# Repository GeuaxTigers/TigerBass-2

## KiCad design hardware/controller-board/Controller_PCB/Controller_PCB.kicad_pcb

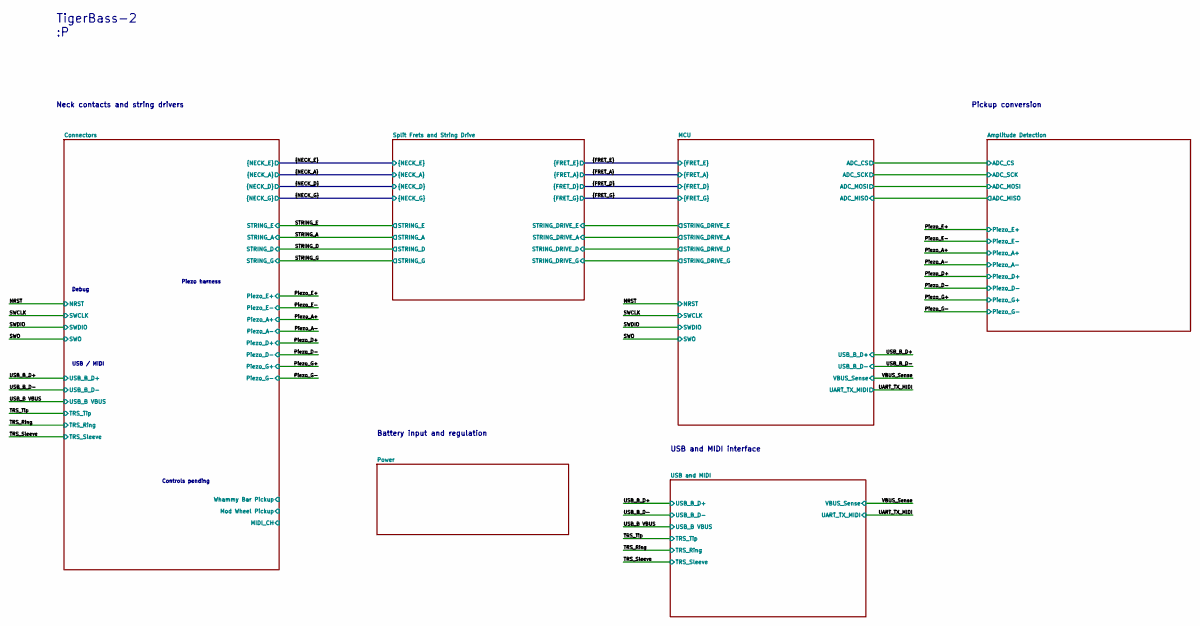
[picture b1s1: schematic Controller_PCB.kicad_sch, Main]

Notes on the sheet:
Pickup conversion
USB and MIDI interface
Debug
Controls pending
Battery input and regulation
Neck contacts and string drivers
Piezo harness
TigerBass-2 :P
USB / MIDI

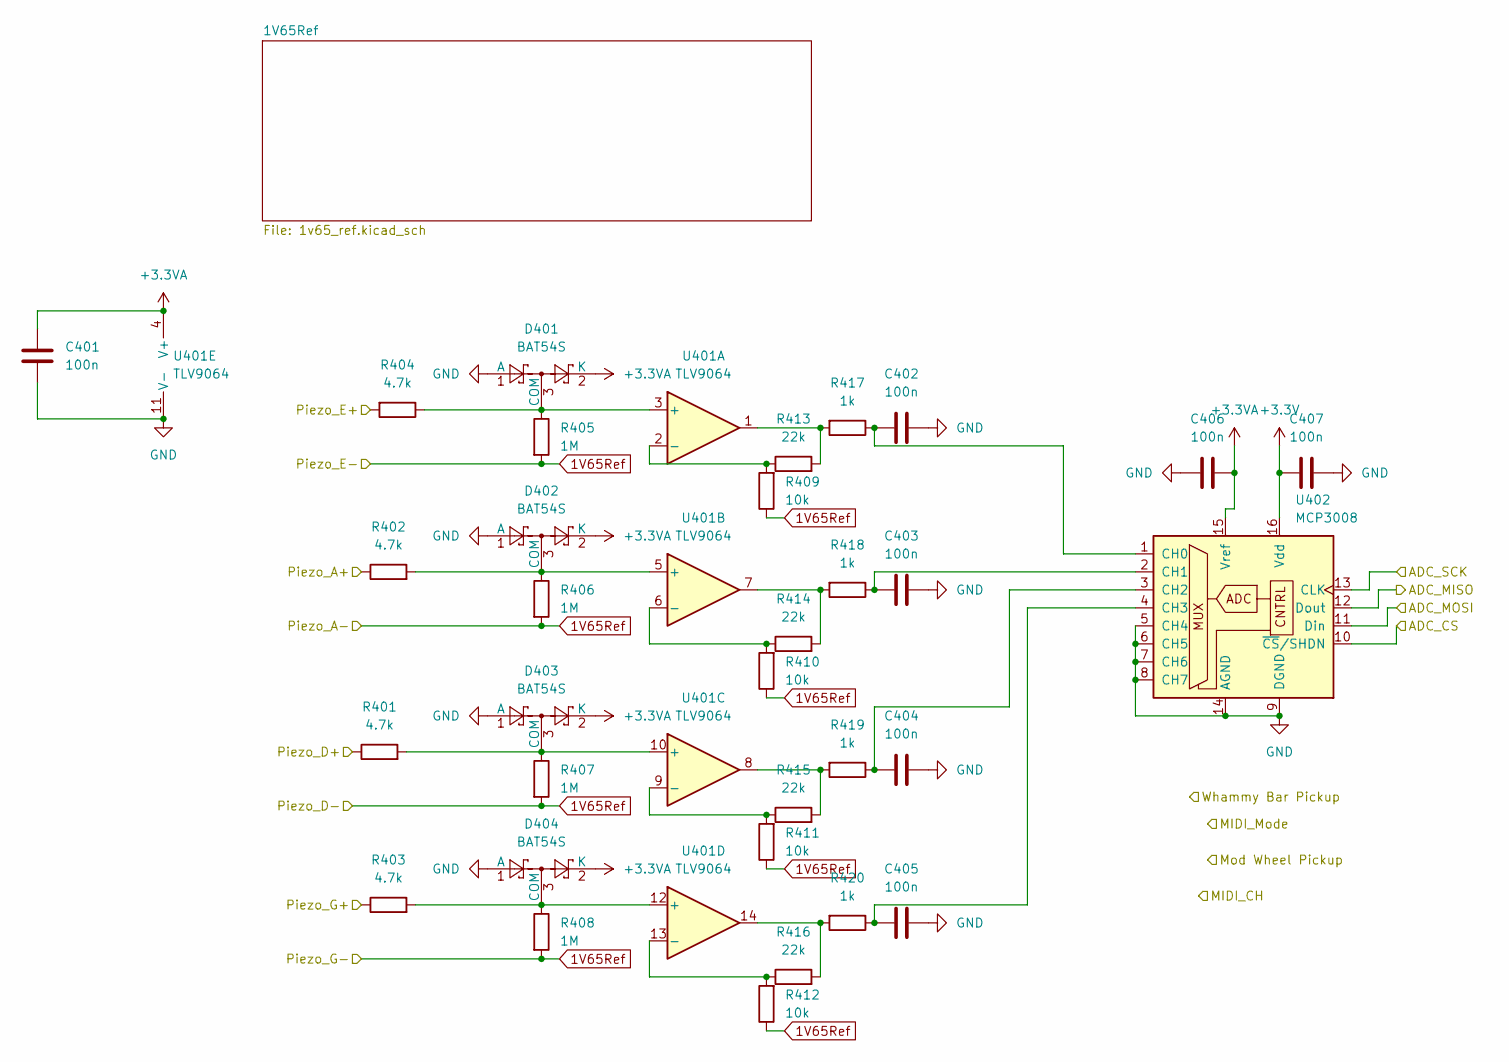
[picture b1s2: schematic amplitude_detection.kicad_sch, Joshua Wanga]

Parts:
C401, C402, C403, C404, C405, C406, C407: 100n; C_0402_1005Metric
D401, D402, D403, D404: BAT54S; SOT-23
R401, R402, R403, R404: 4.7k; R_0402_1005Metric
R405, R406, R407, R408: 1M; R_0402_1005Metric
R409, R410, R411, R412: 10k; R_0402_1005Metric
R413, R414, R415, R416: 22k; R_0402_1005Metric
R417, R418, R419, R420: 1k; R_0402_1005Metric
U401: TLV9064; SOIC127P600X175-14N
U402: MCP3008; SOIC127P600X175-16N

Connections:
1V65Ref: R405.2, R406.2, R407.2, R408.2, R409.1, R410.1, R411.1, R412.1; also elsewhere on the board
+3.3V: C407.1, U402.16 (Vdd); also elsewhere on the board
+3.3VA: C401.2, C406.1, D401.2 (K), D402.2 (K), D403.2 (K), D404.2 (K), U401.4 (V+), U402.15 (Vref); also elsewhere on the board
/Piezo_A+: R402.1
/Piezo_D+: R401.1
/Piezo_E+: R404.2
/Piezo_G+: R403.1
GND: C401.1, C402.2, C403.2, C404.2, C405.2, C406.2, C407.2, D401.1 (A), D402.1 (A), D403.1 (A), D404.1 (A), U401.11 (V-), U402.5 (CH4), U402.6 (CH5), U402.7 (CH6), U402.8 (CH7), U402.9 (DGND), U402.14 (AGND); also elsewhere on the board
unnamed: D401.3 (COM), R404.1, R405.1, U401.3 (+)
unnamed: D402.3 (COM), R402.2, R406.1, U401.5 (+)
unnamed: D403.3 (COM), R401.2, R407.1, U401.10 (+)
unnamed: D404.3 (COM), R403.2, R408.1, U401.12 (+)
unnamed: R413.2, R417.2, U401.1
unnamed: R414.2, R418.2, U401.7
unnamed: R415.2, R419.2, U401.8
unnamed: R416.2, R420.2, U401.14
unnamed: R409.2, R413.1, U401.2 (-)
unnamed: R410.2, R414.1, U401.6 (-)
unnamed: R411.2, R415.1, U401.9 (-)
unnamed: R412.2, R416.1, U401.13 (-)
unnamed: C402.1, R417.1, U402.1 (CH0)
unnamed: C403.1, R418.1, U402.2 (CH1)
unnamed: C404.1, R419.1, U402.3 (CH2)
unnamed: C405.1, R420.1, U402.4 (CH3)

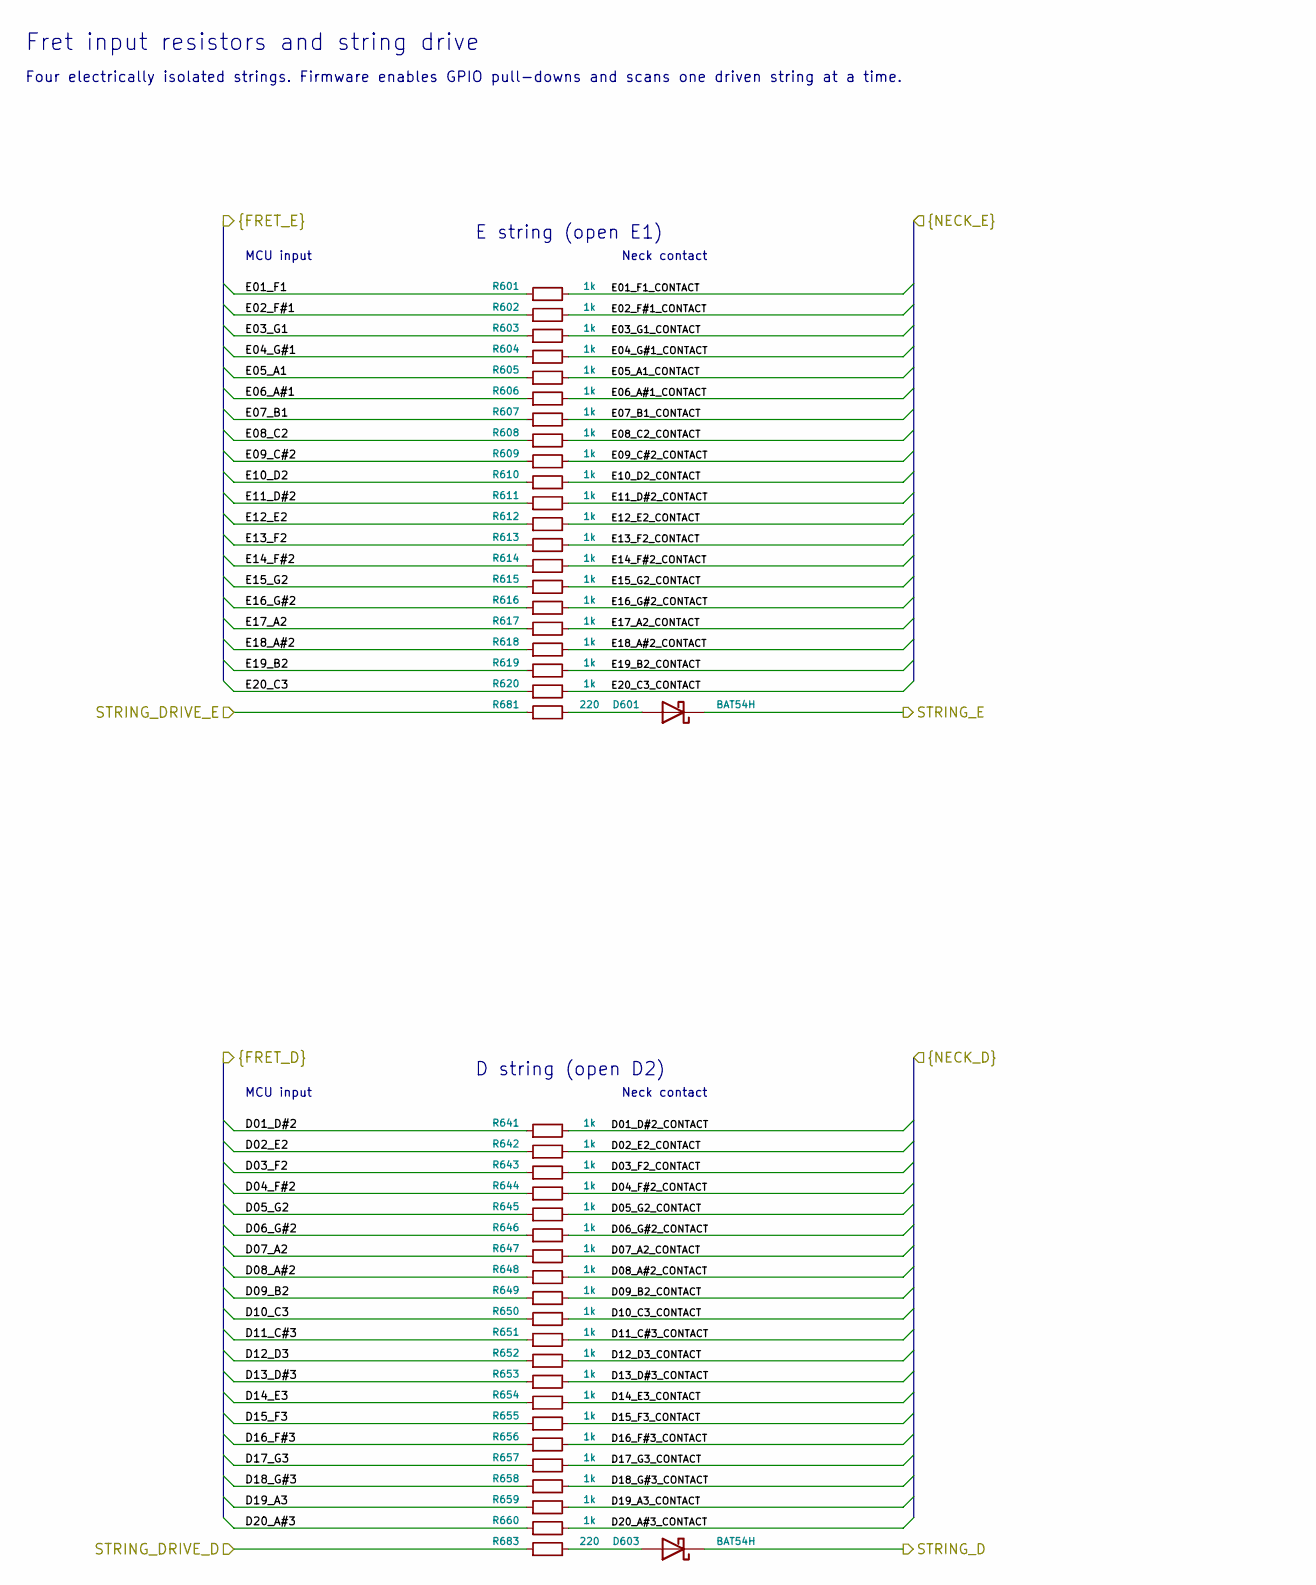
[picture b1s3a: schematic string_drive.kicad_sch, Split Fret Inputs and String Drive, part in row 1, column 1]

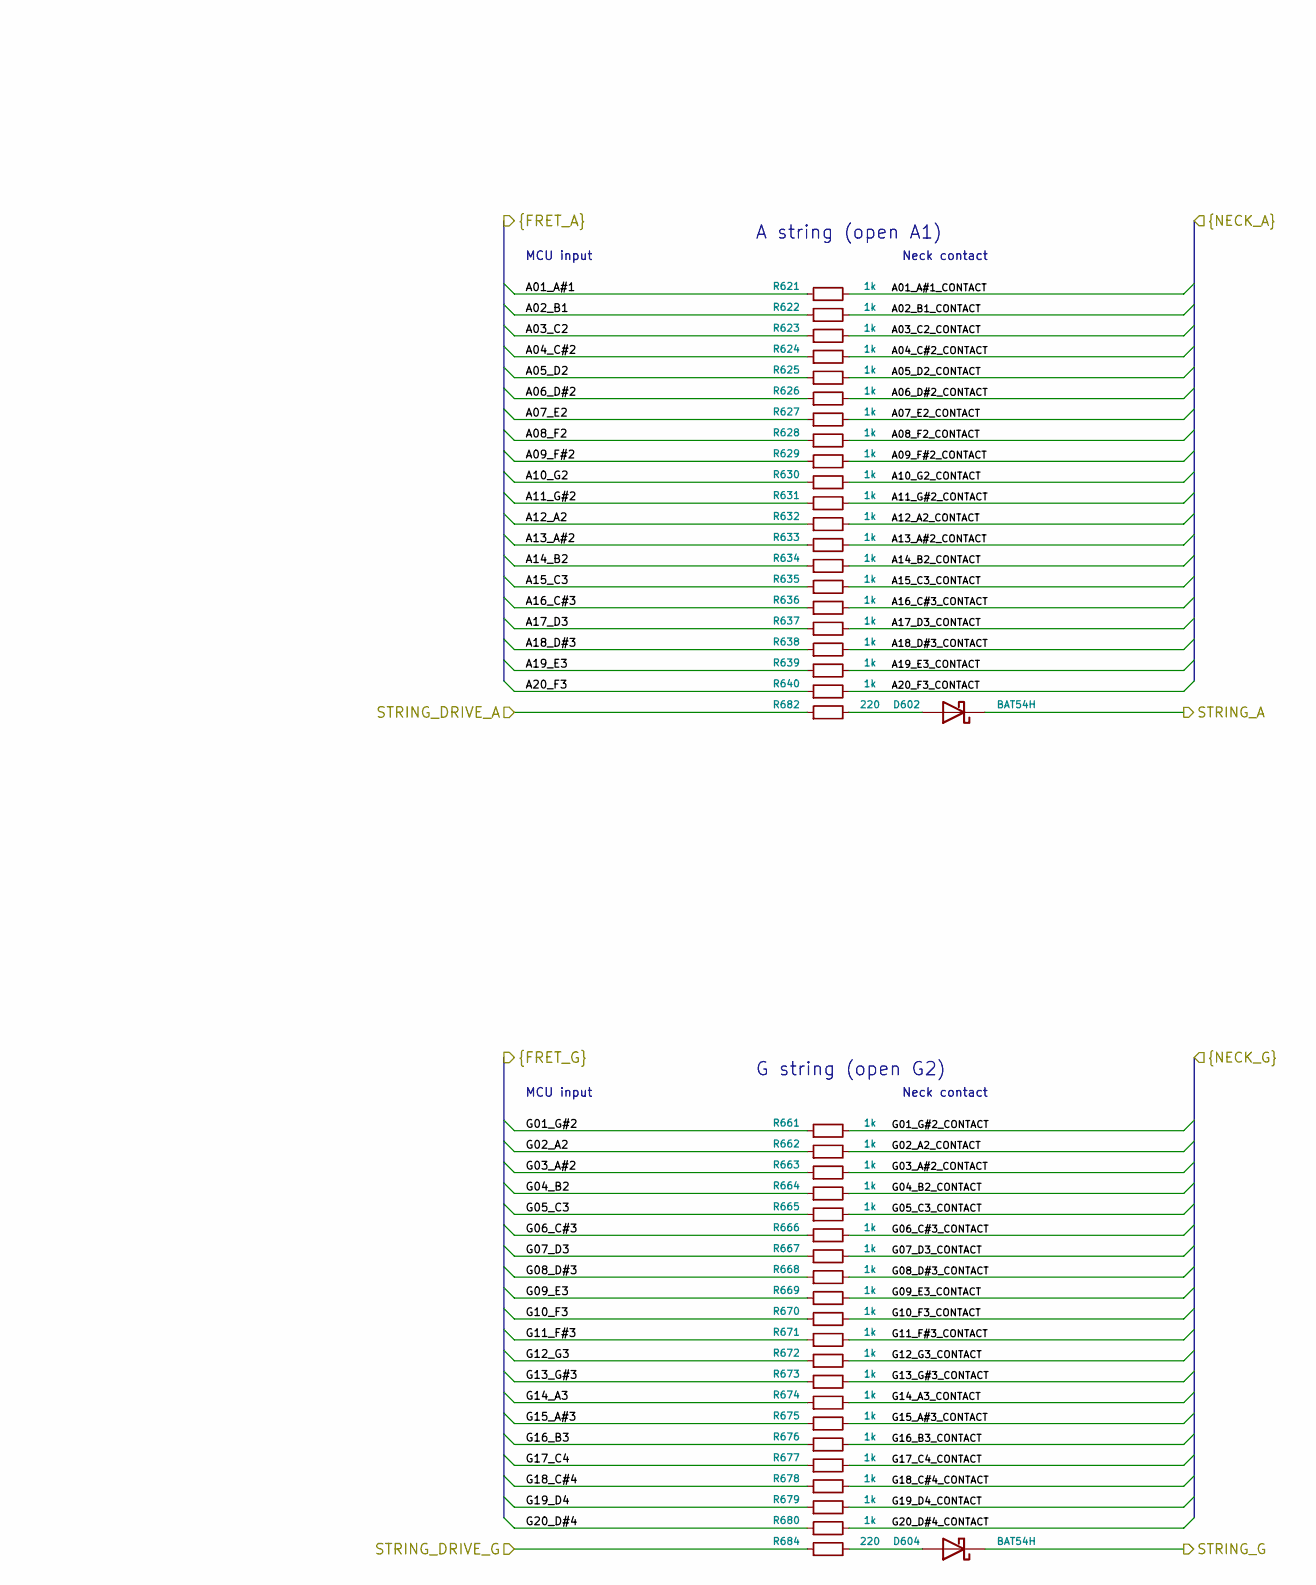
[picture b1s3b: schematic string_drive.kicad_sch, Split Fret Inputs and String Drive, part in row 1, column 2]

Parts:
D601, D602, D603, D604: BAT54H; D_SOD-123F
R601, R602, R603, R604, R605, R606, R607, R608, R609, R610, R611, R612, R613, R614, R615, R616, R617, R618, R619, R620, R621, R622, R623, R624, R625, R626, R627, R628, R629, R630, R631, R632, R633, R634, R635, R636, R637, R638, R639, R640, R641, R642, R643, R644, R645, R646, R647, R648, R649, R650, R651, R652, R653, R654, R655, R656, R657, R658, R659, R660, R661, R662, R663, R664, R665, R666, R667, R668, R669, R670, R671, R672, R673, R674, R675, R676, R677, R678, R679, R680: 1k; R_0603_1608Metric
R681, R682, R683, R684: 220; R_0603_1608Metric

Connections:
/A01_A#1: R621.1; also elsewhere on the board
/A01_A#1_CONTACT: R621.2; also elsewhere on the board
/A02_B1: R622.1; also elsewhere on the board
/A02_B1_CONTACT: R622.2; also elsewhere on the board
/A03_C2: R623.1; also elsewhere on the board
/A03_C2_CONTACT: R623.2; also elsewhere on the board
/A04_C#2: R624.1; also elsewhere on the board
/A04_C#2_CONTACT: R624.2; also elsewhere on the board
/A05_D2: R625.1; also elsewhere on the board
/A05_D2_CONTACT: R625.2; also elsewhere on the board
/A06_D#2: R626.1; also elsewhere on the board
/A06_D#2_CONTACT: R626.2; also elsewhere on the board
/A07_E2: R627.1; also elsewhere on the board
/A07_E2_CONTACT: R627.2; also elsewhere on the board
/A08_F2: R628.1; also elsewhere on the board
/A08_F2_CONTACT: R628.2; also elsewhere on the board
/A09_F#2: R629.1; also elsewhere on the board
/A09_F#2_CONTACT: R629.2; also elsewhere on the board
/A10_G2: R630.1; also elsewhere on the board
/A10_G2_CONTACT: R630.2; also elsewhere on the board
/A11_G#2: R631.1; also elsewhere on the board
/A11_G#2_CONTACT: R631.2; also elsewhere on the board
/A12_A2: R632.1; also elsewhere on the board
/A12_A2_CONTACT: R632.2; also elsewhere on the board
/A13_A#2: R633.1; also elsewhere on the board
/A13_A#2_CONTACT: R633.2; also elsewhere on the board
/A14_B2: R634.1; also elsewhere on the board
/A14_B2_CONTACT: R634.2; also elsewhere on the board
/A15_C3: R635.1; also elsewhere on the board
/A15_C3_CONTACT: R635.2; also elsewhere on the board
/A16_C#3: R636.1; also elsewhere on the board
/A16_C#3_CONTACT: R636.2; also elsewhere on the board
/A17_D3: R637.1; also elsewhere on the board
/A17_D3_CONTACT: R637.2; also elsewhere on the board
/A18_D#3: R638.1; also elsewhere on the board
/A18_D#3_CONTACT: R638.2; also elsewhere on the board
/A19_E3: R639.1; also elsewhere on the board
/A19_E3_CONTACT: R639.2; also elsewhere on the board
/A20_F3: R640.1; also elsewhere on the board
/A20_F3_CONTACT: R640.2; also elsewhere on the board
/D01_D#2: R641.1; also elsewhere on the board
/D01_D#2_CONTACT: R641.2; also elsewhere on the board
/D02_E2: R642.1; also elsewhere on the board
/D02_E2_CONTACT: R642.2; also elsewhere on the board
/D03_F2: R643.1; also elsewhere on the board
/D03_F2_CONTACT: R643.2; also elsewhere on the board
/D04_F#2: R644.1; also elsewhere on the board
/D04_F#2_CONTACT: R644.2; also elsewhere on the board
/D05_G2: R645.1; also elsewhere on the board
/D05_G2_CONTACT: R645.2; also elsewhere on the board
/D06_G#2: R646.1; also elsewhere on the board
/D06_G#2_CONTACT: R646.2; also elsewhere on the board
/D07_A2: R647.1; also elsewhere on the board
/D07_A2_CONTACT: R647.2; also elsewhere on the board
/D08_A#2: R648.1; also elsewhere on the board
/D08_A#2_CONTACT: R648.2; also elsewhere on the board
/D09_B2: R649.1; also elsewhere on the board
/D09_B2_CONTACT: R649.2; also elsewhere on the board
/D10_C3: R650.1; also elsewhere on the board
/D10_C3_CONTACT: R650.2; also elsewhere on the board
/D11_C#3: R651.1; also elsewhere on the board
/D11_C#3_CONTACT: R651.2; also elsewhere on the board
/D12_D3: R652.1; also elsewhere on the board
/D12_D3_CONTACT: R652.2; also elsewhere on the board
/D13_D#3: R653.1; also elsewhere on the board
/D13_D#3_CONTACT: R653.2; also elsewhere on the board
/D14_E3: R654.1; also elsewhere on the board
/D14_E3_CONTACT: R654.2; also elsewhere on the board
/D15_F3: R655.1; also elsewhere on the board
/D15_F3_CONTACT: R655.2; also elsewhere on the board
/D16_F#3: R656.1; also elsewhere on the board
/D16_F#3_CONTACT: R656.2; also elsewhere on the board
/D17_G3: R657.1; also elsewhere on the board
/D17_G3_CONTACT: R657.2; also elsewhere on the board
/D18_G#3: R658.1; also elsewhere on the board
/D18_G#3_CONTACT: R658.2; also elsewhere on the board
/D19_A3: R659.1; also elsewhere on the board
/D19_A3_CONTACT: R659.2; also elsewhere on the board
/D20_A#3: R660.1; also elsewhere on the board
/D20_A#3_CONTACT: R660.2; also elsewhere on the board
/E01_F1: R601.1; also elsewhere on the board
/E01_F1_CONTACT: R601.2; also elsewhere on the board
/E02_F#1: R602.1; also elsewhere on the board
/E02_F#1_CONTACT: R602.2; also elsewhere on the board
/E03_G1: R603.1; also elsewhere on the board
/E03_G1_CONTACT: R603.2; also elsewhere on the board
/E04_G#1: R604.1; also elsewhere on the board
/E04_G#1_CONTACT: R604.2; also elsewhere on the board
/E05_A1: R605.1; also elsewhere on the board
/E05_A1_CONTACT: R605.2; also elsewhere on the board
/E06_A#1: R606.1; also elsewhere on the board
/E06_A#1_CONTACT: R606.2; also elsewhere on the board
/E07_B1: R607.1; also elsewhere on the board
/E07_B1_CONTACT: R607.2; also elsewhere on the board
/E08_C2: R608.1; also elsewhere on the board
/E08_C2_CONTACT: R608.2; also elsewhere on the board
/E09_C#2: R609.1; also elsewhere on the board
/E09_C#2_CONTACT: R609.2; also elsewhere on the board
/E10_D2: R610.1; also elsewhere on the board
/E10_D2_CONTACT: R610.2; also elsewhere on the board
/E11_D#2: R611.1; also elsewhere on the board
/E11_D#2_CONTACT: R611.2; also elsewhere on the board
/E12_E2: R612.1; also elsewhere on the board
/E12_E2_CONTACT: R612.2; also elsewhere on the board
/E13_F2: R613.1; also elsewhere on the board
/E13_F2_CONTACT: R613.2; also elsewhere on the board
/E14_F#2: R614.1; also elsewhere on the board
/E14_F#2_CONTACT: R614.2; also elsewhere on the board
/E15_G2: R615.1; also elsewhere on the board
/E15_G2_CONTACT: R615.2; also elsewhere on the board
/E16_G#2: R616.1; also elsewhere on the board
/E16_G#2_CONTACT: R616.2; also elsewhere on the board
/E17_A2: R617.1; also elsewhere on the board
/E17_A2_CONTACT: R617.2; also elsewhere on the board
/E18_A#2: R618.1; also elsewhere on the board
/E18_A#2_CONTACT: R618.2; also elsewhere on the board
/E19_B2: R619.1; also elsewhere on the board
/E19_B2_CONTACT: R619.2; also elsewhere on the board
/E20_C3: R620.1; also elsewhere on the board
/E20_C3_CONTACT: R620.2; also elsewhere on the board
/G01_G#2: R661.1; also elsewhere on the board
/G01_G#2_CONTACT: R661.2; also elsewhere on the board
/G02_A2: R662.1; also elsewhere on the board
/G02_A2_CONTACT: R662.2; also elsewhere on the board
/G03_A#2: R663.1; also elsewhere on the board
/G03_A#2_CONTACT: R663.2; also elsewhere on the board
/G04_B2: R664.1; also elsewhere on the board
/G04_B2_CONTACT: R664.2; also elsewhere on the board
/G05_C3: R665.1; also elsewhere on the board
/G05_C3_CONTACT: R665.2; also elsewhere on the board
/G06_C#3: R666.1; also elsewhere on the board
/G06_C#3_CONTACT: R666.2; also elsewhere on the board
/G07_D3: R667.1; also elsewhere on the board
/G07_D3_CONTACT: R667.2; also elsewhere on the board
/G08_D#3: R668.1; also elsewhere on the board
/G08_D#3_CONTACT: R668.2; also elsewhere on the board
/G09_E3: R669.1; also elsewhere on the board
/G09_E3_CONTACT: R669.2; also elsewhere on the board
/G10_F3: R670.1; also elsewhere on the board
/G10_F3_CONTACT: R670.2; also elsewhere on the board
/G11_F#3: R671.1; also elsewhere on the board
/G11_F#3_CONTACT: R671.2; also elsewhere on the board
/G12_G3: R672.1; also elsewhere on the board
/G12_G3_CONTACT: R672.2; also elsewhere on the board
/G13_G#3: R673.1; also elsewhere on the board
/G13_G#3_CONTACT: R673.2; also elsewhere on the board
/G14_A3: R674.1; also elsewhere on the board
/G14_A3_CONTACT: R674.2; also elsewhere on the board
/G15_A#3: R675.1; also elsewhere on the board
/G15_A#3_CONTACT: R675.2; also elsewhere on the board
/G16_B3: R676.1; also elsewhere on the board
/G16_B3_CONTACT: R676.2; also elsewhere on the board
/G17_C4: R677.1; also elsewhere on the board
/G17_C4_CONTACT: R677.2; also elsewhere on the board
/G18_C#4: R678.1; also elsewhere on the board
/G18_C#4_CONTACT: R678.2; also elsewhere on the board
/G19_D4: R679.1; also elsewhere on the board
/G19_D4_CONTACT: R679.2; also elsewhere on the board
/G20_D#4: R680.1; also elsewhere on the board
/G20_D#4_CONTACT: R680.2; also elsewhere on the board
/STRING_A: D602.1 (K); also elsewhere on the board
/STRING_D: D603.1 (K); also elsewhere on the board
/STRING_E: D601.1 (K); also elsewhere on the board
/STRING_G: D604.1 (K); also elsewhere on the board
/Split Frets and String Drive/STRING_DRIVE_A: R682.1
/Split Frets and String Drive/STRING_DRIVE_D: R683.1
/Split Frets and String Drive/STRING_DRIVE_E: R681.1
/Split Frets and String Drive/STRING_DRIVE_G: R684.1
unnamed: D601.2 (A), R681.2
unnamed: D602.2 (A), R682.2
unnamed: D603.2 (A), R683.2
unnamed: D604.2 (A), R684.2

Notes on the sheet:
Fret input resistors and string drive
E string (open E1)
MCU input
Neck contact
G string (open G2)
D string (open D2)
Four electrically isolated strings. Firmware enables GPIO pull-downs and scans one driven string at a time.
A string (open A1)

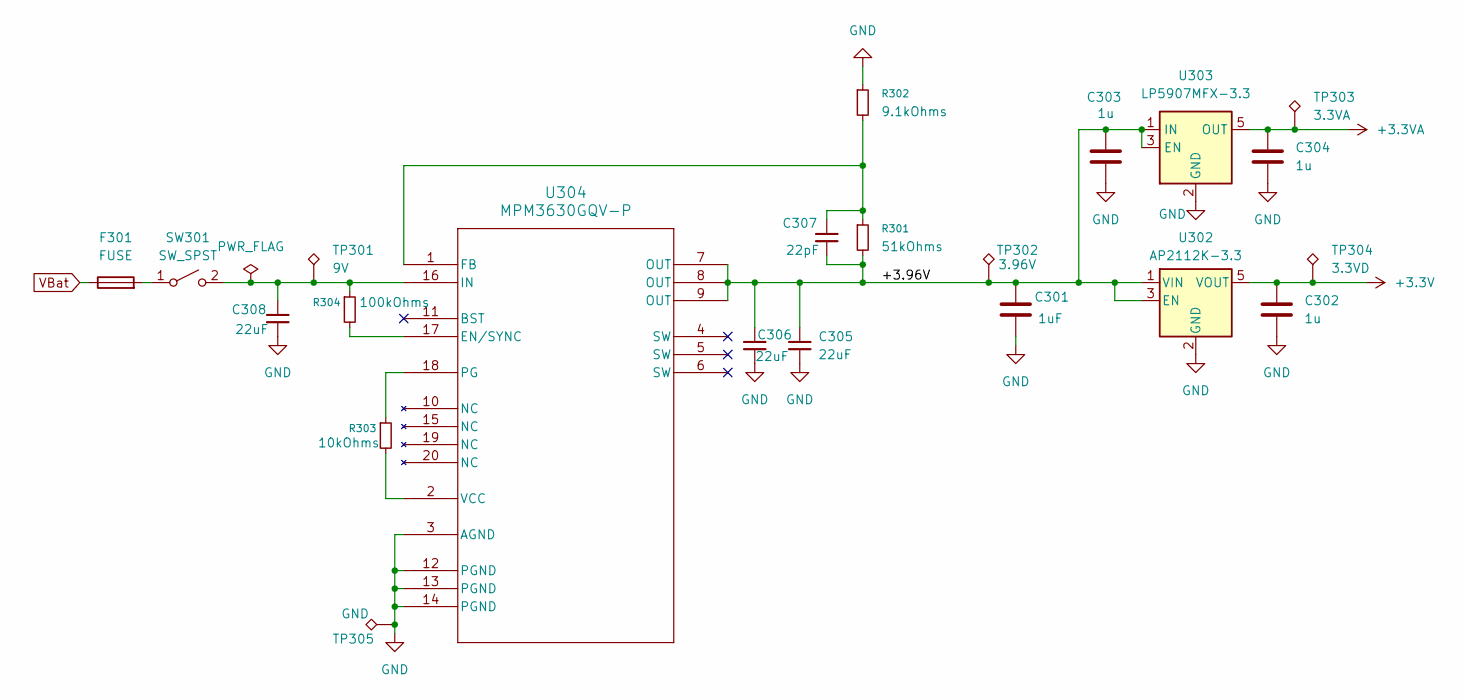
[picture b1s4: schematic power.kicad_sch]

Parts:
C301: 1uF; C_0402_1005Metric
C302, C303, C304: 1u; C_0402_1005Metric
C305, C306, C308: 22uF
C307: 22pF
F301: FUSE; Fuse_0402_1005Metric_Pad0.77x0.64mm_HandSolder
R301: 51kOhms
R302: 9.1kOhms
R303: 10kOhms
R304: 100kOhms
SW301: SW_SPST; PinHeader_1x02_P2.54mm_Vertical
TP301: 9V; TestPoint_Pad_D2.0mm
TP302: 3.96V; TestPoint_Pad_D2.0mm
TP303: 3.3VA; TestPoint_Pad_D2.0mm
TP304: 3.3VD; TestPoint_Pad_D2.0mm
TP305: GND; TestPoint_Pad_D2.0mm
U302: AP2112K-3.3; SOT-23-5
U303: LP5907MFX-3.3; SOT-23-5
U304: MPM3630GQV-P; QFN3p0x5p0x1p6_MPM3630_MNP

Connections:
+3.3V: C302.1, TP304.1 (1_1), U302.5 (VOUT); also elsewhere on the board
+3.3VA: C304.1, TP303.1 (1_1), U303.5 (OUT); also elsewhere on the board
/Power/+3.96V: C301.1, C303.1, C305.1, C306.1, C307.2, R301.2, TP302.1 (1_1), U302.1 (VIN), U302.3 (EN), U303.1 (IN), U303.3 (EN), U304.7 (OUT), U304.8 (OUT), U304.9 (OUT)
GND: C301.2, C302.2, C303.2, C304.2, C305.2, C306.2, C308.2, R302.1, TP305.1 (1_1), U302.2 (GND), U303.2 (GND), U304.3 (AGND), U304.12 (PGND), U304.13 (PGND), U304.14 (PGND); also elsewhere on the board
unnamed: C307.1, R301.1, R302.2, U304.1 (FB)
unnamed: R303.1, U304.18 (PG)
unnamed: R303.2, U304.2 (VCC)
unnamed: R304.2, U304.17 (EN/SYNC)
unnamed: F301.2, SW301.1 (A)
unnamed: C308.1, R304.1, SW301.2 (B), TP301.1 (1_1), U304.16 (IN)
VBat: F301.1

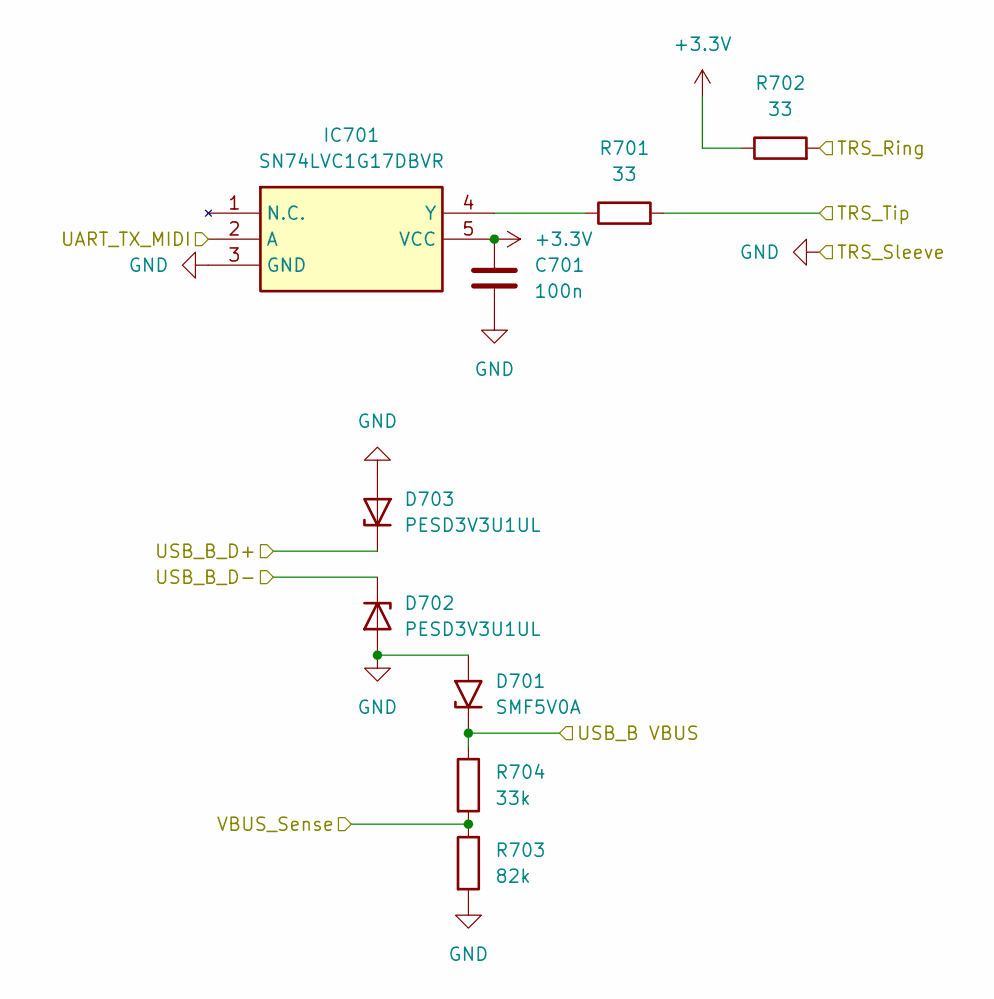
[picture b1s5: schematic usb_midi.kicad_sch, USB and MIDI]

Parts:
C701: 100n; C_0402_1005Metric
D701: SMF5V0A; D_SMF
D702, D703: PESD3V3U1UL; D_SOD-882
IC701: SN74LVC1G17DBVR; SOT95P280X145-5N; Manufacturer_Part_Number SN74LVC1G17DBVR; Mouser Part Number 595-SN74LVC1G17DBVR
R701, R702: 33; R_0402_1005Metric
R703: 82k; R_0402_1005Metric
R704: 33k; R_0402_1005Metric

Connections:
+3.3V: C701.1, IC701.5 (VCC), R702.1; also elsewhere on the board
/TRS_Ring: R702.2
/TRS_Tip: R701.2
/USB_B VBUS: D701.1 (A1), R704.1
/USB_B_D+: D703.1 (K); also elsewhere on the board
/USB_B_D-: D702.1 (K); also elsewhere on the board
/VBUS_Sense: R703.1, R704.2; also elsewhere on the board
GND: C701.2, D701.2 (A2), D702.2 (A), D703.2 (A), IC701.3 (GND), R703.2; also elsewhere on the board
unnamed: IC701.4 (Y), R701.1
